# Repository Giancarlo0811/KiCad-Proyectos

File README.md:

# KiCad-Proyectos
Repositorio con diseños de PCB usando KiCad 8.0

## Diseños PCB

- ### [P1 Linterna LED](./P1_LED_torch)

- ### [P2 Fuente de Poder para Protoboard](./P2_Protoboard_Power_Supply/)

- ### [P3 Reloj Matriz LED 4x8x8 ](./P3_4x8x8_LED_Matrix_Clock/)

- ### [P4 Regulador de Voltaje Lineal de 5V](./P4_Regulador_Voltaje_5V/)

- ### [P5 Datalogger con Microcontrolador](./P5_MCU_Datalogger/)

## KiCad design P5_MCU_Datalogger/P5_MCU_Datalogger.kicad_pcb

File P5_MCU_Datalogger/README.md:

# P5 MCU Datalogger
Diseño de PCB para un datalogger con microcontrolador. El datalogger se basa en un microcontrolador Atmega 328P-AU y cuenta con dos EEPROMs y un reloj en tiempo real.
Componentes adicionales en la placa, como LEDs de estado con sus resistencias, dos osciladores de cristal, conectores y capacitores.

## Esquemático

## Layout

## PCB

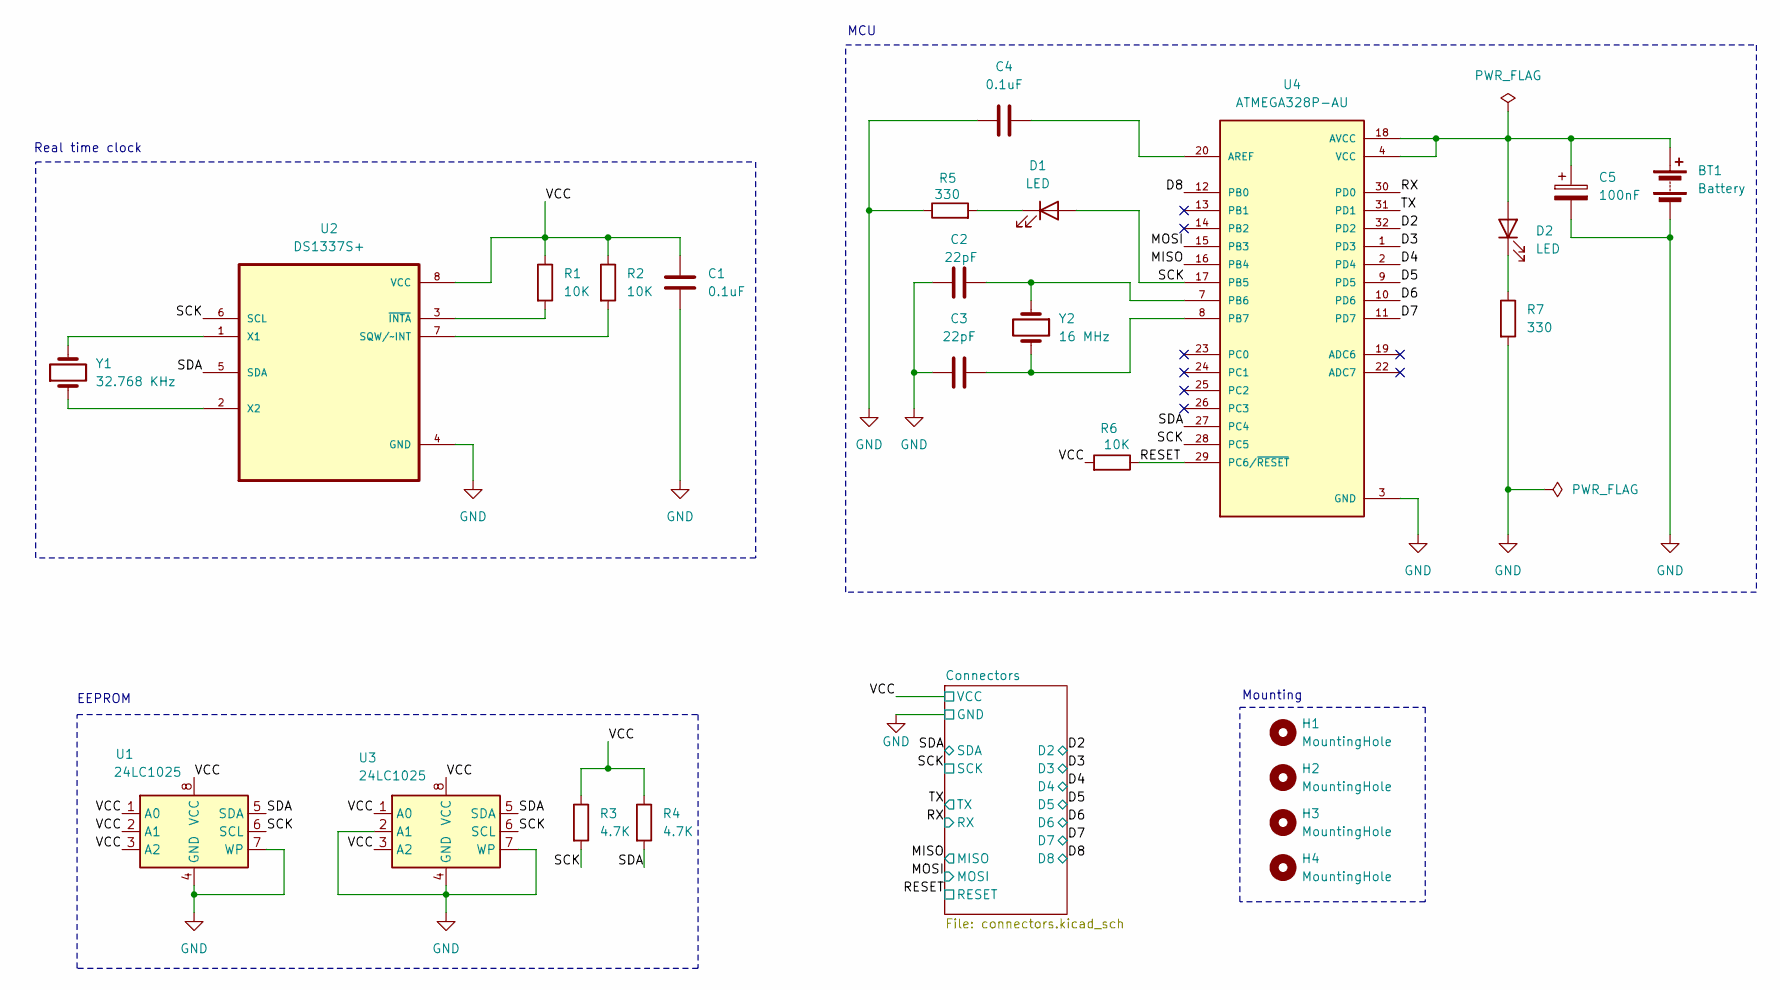
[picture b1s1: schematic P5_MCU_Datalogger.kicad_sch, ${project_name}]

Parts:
BT1: Battery; PinHeader_1x02_P2.54mm_Vertical
C1, C4: 0.1uF; C_0805_2012Metric
C2, C3: 22pF; C_0805_2012Metric
C5: 100nF; CP_Elec_3x5.3
D1, D2: LED; LED_0805_2012Metric
H1, H2, H3, H4: MountingHole; MountingHole_2.1mm
R1, R2, R6: 10K; R_0805_2012Metric
R3, R4: 4.7K; R_0805_2012Metric
R5, R7: 330; R_0805_2012Metric
U1, U3: 24LC1025; SOIC-8-1EP_3.9x4.9mm_P1.27mm_EP2.29x3mm
U2: DS1337S+; SOIC127P600X175-8N
U4: ATMEGA328P-AU; QFP80P900X900X120-32N; PARTREV 8271A
Y1: 32.768 KHz; Crystal_SMD_5032-2Pin_5.0x3.2mm_HandSoldering
Y2: 16 MHz; Crystal_SMD_5032-2Pin_5.0x3.2mm_HandSoldering

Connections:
/D2: U4.32 (PD2); also elsewhere on the board
/D3: U4.1 (PD3); also elsewhere on the board
/D4: U4.2 (PD4); also elsewhere on the board
/D5: U4.9 (PD5); also elsewhere on the board
/D6: U4.10 (PD6); also elsewhere on the board
/D7: U4.11 (PD7); also elsewhere on the board
/D8: U4.12 (PB0); also elsewhere on the board
/MISO: U4.16 (PB4); also elsewhere on the board
/MOSI: U4.15 (PB3); also elsewhere on the board
/RESET: R6.1, U4.29 (PC6/~RESET); also elsewhere on the board
/RX: U4.30 (PD0); also elsewhere on the board
/SCK: D1.2 (A), R3.2, U1.6 (SCL), U2.6 (SCL), U3.6 (SCL), U4.17 (PB5), U4.28 (PC5); also elsewhere on the board
/SDA: R4.2, U1.5 (SDA), U2.5 (SDA), U3.5 (SDA), U4.27 (PC4); also elsewhere on the board
/TX: U4.31 (PD1); also elsewhere on the board
GND: BT1.2 (-), C1.2, C2.1, C3.2, C4.2, C5.2, R5.1, R7.2, U1.4 (GND), U1.7 (WP), U2.4 (GND), U3.2 (A1), U3.4 (GND), U3.7 (WP), U4.3 (GND), U4.5 (GND), U4.21 (GND); also elsewhere on the board
unnamed: D1.1 (K), R5.2
unnamed: D2.1 (K), R7.1
unnamed: R2.2, U2.7 (SQW/~INT)
unnamed: U2.1 (X1), Y1.2
unnamed: U2.2 (X2), Y1.1
unnamed: R1.2, U2.3 (~INTA)
unnamed: C4.1, U4.20 (AREF)
unnamed: C2.2, U4.7 (PB6), Y2.1
unnamed: C3.1, U4.8 (PB7), Y2.2

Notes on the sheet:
Mounting
MCU
EEPROM
Real time clock

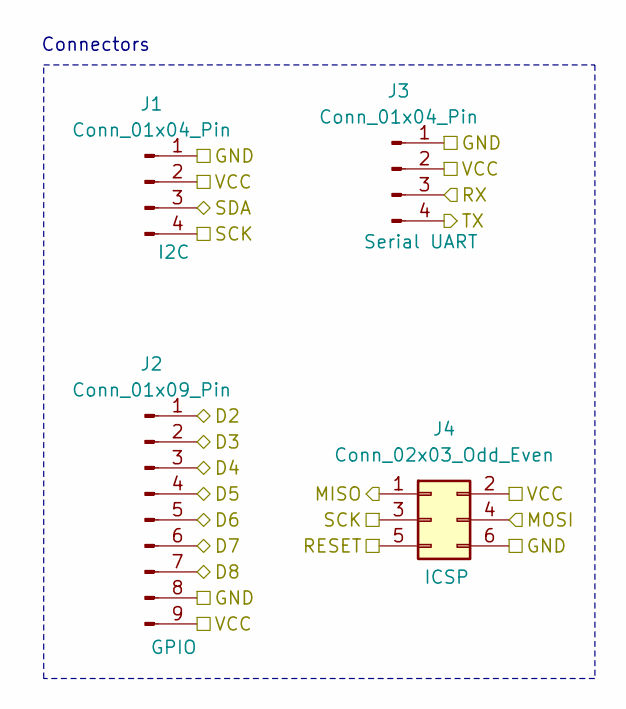
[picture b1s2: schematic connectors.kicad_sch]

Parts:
J1, J3: Conn_01x04_Pin; PinHeader_1x04_P2.54mm_Vertical
J2: Conn_01x09_Pin; PinHeader_1x09_P2.54mm_Vertical
J4: Conn_02x03_Odd_Even; PinHeader_2x03_P2.54mm_Vertical

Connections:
/D2: J2.1; also elsewhere on the board
/D3: J2.2; also elsewhere on the board
/D4: J2.3; also elsewhere on the board
/D5: J2.4; also elsewhere on the board
/D6: J2.5; also elsewhere on the board
/D7: J2.6; also elsewhere on the board
/D8: J2.7; also elsewhere on the board
/MISO: J4.1; also elsewhere on the board
/MOSI: J4.4; also elsewhere on the board
/RESET: J4.5; also elsewhere on the board
/RX: J3.3; also elsewhere on the board
/SCK: J1.4, J4.3; also elsewhere on the board
/SDA: J1.3; also elsewhere on the board
/TX: J3.4; also elsewhere on the board
GND: J1.1, J2.8, J3.1, J4.6; also elsewhere on the board

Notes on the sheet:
Connectors

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
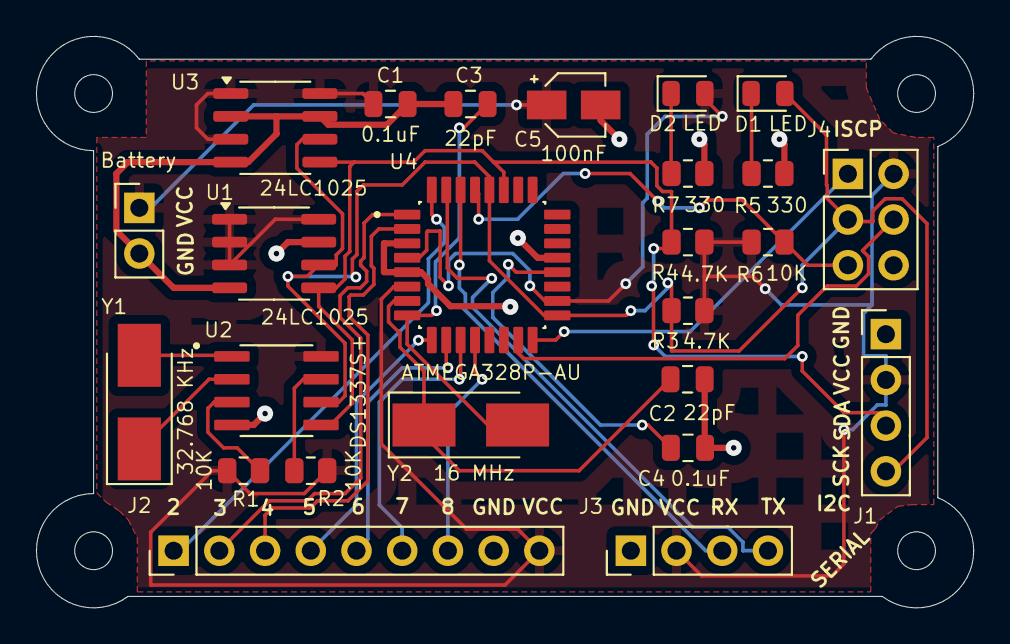
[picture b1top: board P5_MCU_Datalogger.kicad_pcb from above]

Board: 2 copper layers, 52.1 x 31.7 mm, 29 parts (0 on the bottom side), 25 nets.

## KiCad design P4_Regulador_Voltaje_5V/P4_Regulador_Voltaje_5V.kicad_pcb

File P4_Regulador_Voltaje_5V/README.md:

# P4 5V Voltage Regulator
Diseño de PCB para circuito regulador de 5V utilizando el regulador lineal LM2940.

- Voltaje de entrada: 7-35V DC

- Voltaje de salida regulado: 5V DC

## Esquemático

## Layout

## PCB

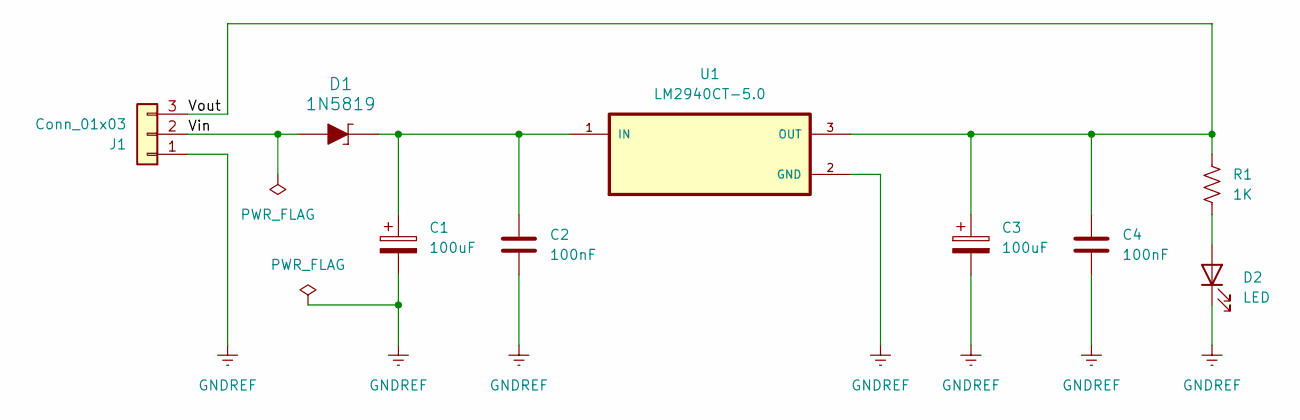
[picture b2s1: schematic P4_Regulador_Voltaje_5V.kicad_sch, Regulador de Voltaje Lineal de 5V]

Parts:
C1, C3: 100uF; CP_Radial_D10.0mm_P5.00mm
C2, C4: 100nF; C_Disc_D5.0mm_W2.5mm_P5.00mm
D1: 1N5819; D_DO-35_SOD27_P10.16mm_Horizontal; MPN 1N5819; Digi-Key_PN 1N5819FSCT-ND
D2: LED; LED_D5.0mm
J1: Conn_01x03; PinHeader_1x03_P2.54mm_Horizontal
R1: 1K; R_Axial_DIN0207_L6.3mm_D2.5mm_P7.62mm_Horizontal
U1: LM2940CT-5.0; TO254P1054X470X1955-3

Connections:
/Vin: D1.2, J1.2
/Vout: C3.1, C4.1, J1.3, R1.1, U1.3 (OUT)
GNDREF: C1.2, C2.2, C3.2, C4.2, D2.1 (K), J1.1, U1.2 (GND)
unnamed: D2.2 (A), R1.2
unnamed: C1.1, C2.1, D1.1, U1.1 (IN)

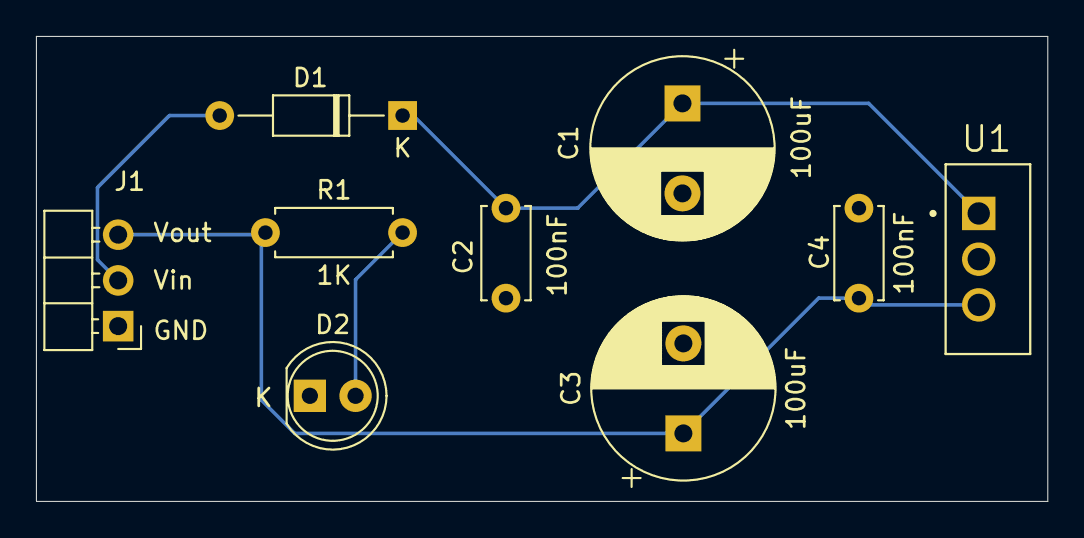
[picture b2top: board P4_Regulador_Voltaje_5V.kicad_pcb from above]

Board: 2 copper layers, 56.2 x 25.8 mm, 9 parts (0 on the bottom side), 5 nets.

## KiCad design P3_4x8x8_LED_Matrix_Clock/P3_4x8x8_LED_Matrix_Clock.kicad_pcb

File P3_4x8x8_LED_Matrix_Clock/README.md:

# P3 4x8x8 LED Matrix Clock
Diseño de PCB que puede tener cuatro pantallas de matriz LED de 8x8 controladas por un Arduino Pro
mini. 

La placa también incluye dos botones a los que se pueden asignar funciones arbitrarias.
Un posible uso puede ser un temporizador Pomodoro: Un botón para seleccionar la duración de la vuelta (por ejemplo, 15, 20 o 25 minutos) y el otro para reiniciar el temporizador. Cuando se acabe el tiempo establecido, la pantalla parpadeará para avisar.

## Esquemático

## Layout

## PCB

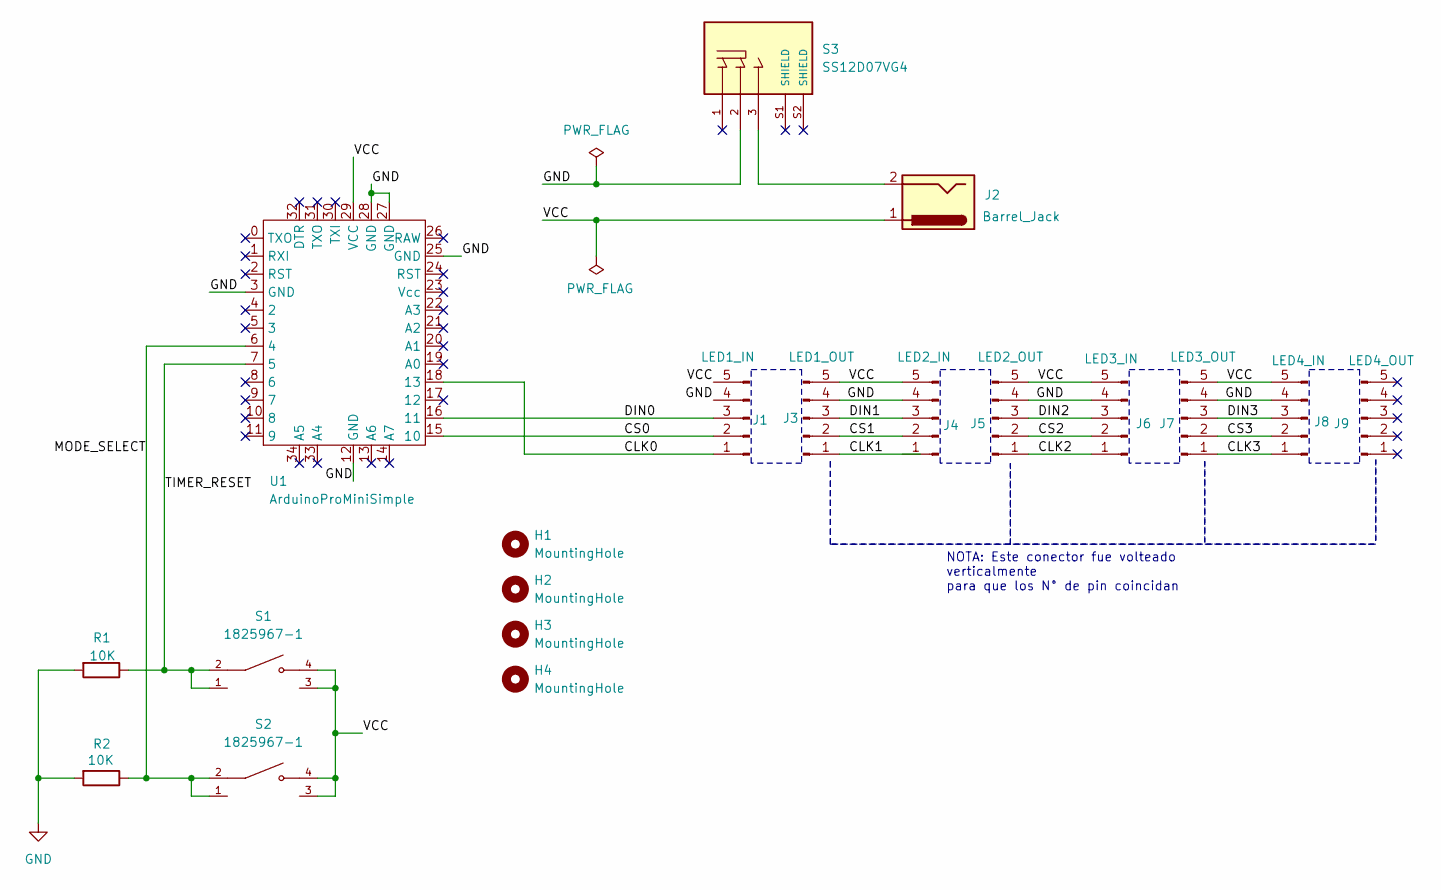
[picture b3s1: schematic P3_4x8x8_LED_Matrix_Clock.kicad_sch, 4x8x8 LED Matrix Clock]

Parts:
H1, H2, H3, H4: MountingHole; MountingHole_2.5mm
J1: LED1_IN; PinHeader_1x05_P2.54mm_Vertical
J2: Barrel_Jack; BarrelJack_Horizontal
J3: LED1_OUT; PinSocket_1x05_P2.54mm_Vertical
J4: LED2_IN; PinSocket_1x05_P2.54mm_Vertical
J5: LED2_OUT; PinSocket_1x05_P2.54mm_Vertical
J6: LED3_IN; PinSocket_1x05_P2.54mm_Vertical
J7: LED3_OUT; PinSocket_1x05_P2.54mm_Vertical
J8: LED4_IN; PinSocket_1x05_P2.54mm_Vertical
J9: LED4_OUT; PinSocket_1x05_P2.54mm_Vertical
R1, R2: 10K; R_Axial_DIN0204_L3.6mm_D1.6mm_P7.62mm_Horizontal
S1, S2: 1825967-1; SW_1825967-1
S3: SS12D07VG4; SW_SS12D07VG4; PARTREV 1
U1: ArduinoProMiniSimple; ArduinoProMiniCustom

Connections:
/CLK0: J1.1, U1.18 (13)
/CLK1: J3.1
/CLK2: J5.1, J6.1
/CLK3: J7.1, J8.1
/CS0: J1.2, U1.15 (10)
/CS1: J3.2, J4.2
/CS2: J5.2, J6.2
/CS3: J7.2, J8.2
/DIN0: J1.3, U1.16 (11)
/DIN1: J3.3, J4.3
/DIN2: J5.3, J6.3
/DIN3: J7.3, J8.3
/MODE_SELECT: R2.1, S2.1, S2.2, U1.6 (4)
/TIMER_RESET: R1.1, S1.1, S1.2, U1.7 (5)
/VCC: J1.5, J2.1, J3.5, J4.5, J5.5, J6.5, J7.5, J8.5, S1.3, S1.4, S2.3, S2.4, U1.29 (VCC)
GND: J1.4, J3.4, J4.4, J5.4, J6.4, J7.4, J8.4, R1.2, R2.2, S3.2, U1.3 (GND), U1.12 (GND), U1.25 (GND), U1.27 (GND), U1.28 (GND)
unnamed: J2.2, S3.3

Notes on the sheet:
NOTA: Este conector fue volteado verticalmente para que los N° de pin coincidan

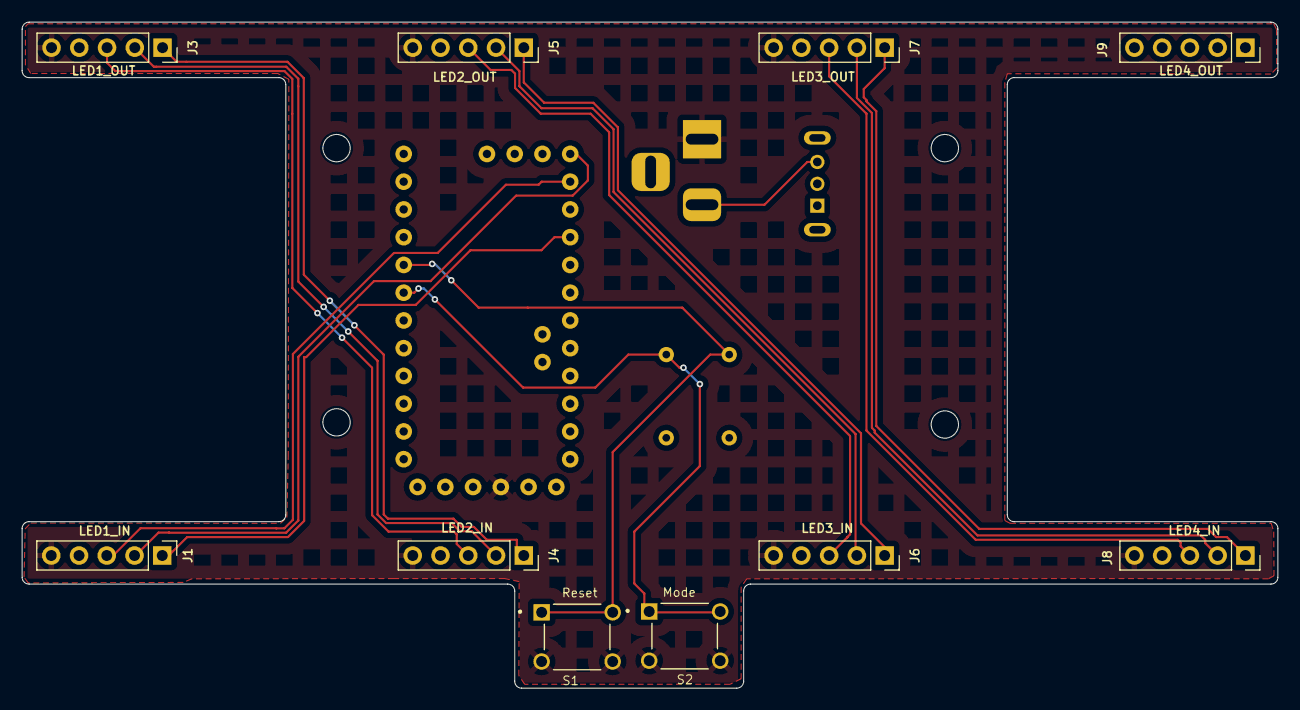
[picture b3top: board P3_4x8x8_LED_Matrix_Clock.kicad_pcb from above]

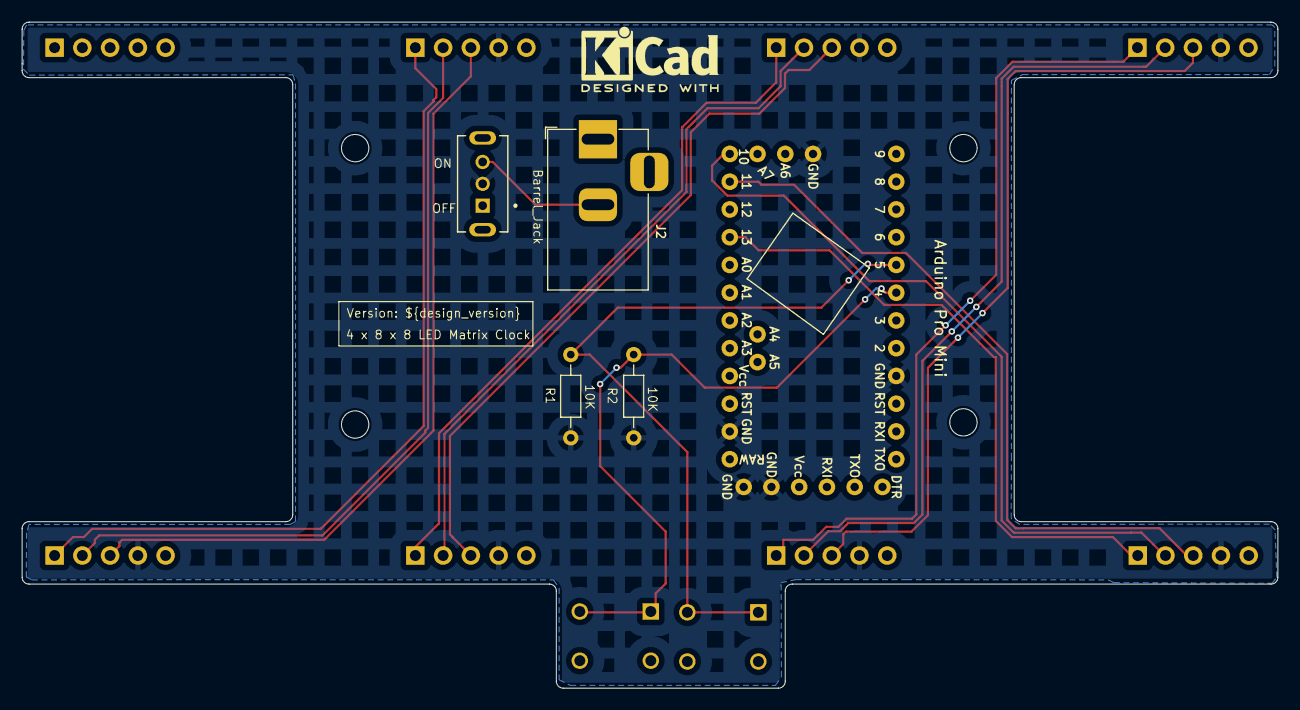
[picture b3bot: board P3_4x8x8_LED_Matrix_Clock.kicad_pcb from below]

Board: 2 copper layers, 114.9 x 61.0 mm, 20 parts (6 on the bottom side), 16 nets.

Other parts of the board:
Kicad_Logo: KiCad-Logo2_5mm_SilkScreen

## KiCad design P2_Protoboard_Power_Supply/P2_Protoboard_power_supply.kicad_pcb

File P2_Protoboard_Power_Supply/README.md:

# P1 Protoboard Power Supply
Diseño de una fuente de poder para protoboard.
- Puede conectarse directamente a la protoboard
- On/Off switch
- Puede proveer 5V y 3.3V
- Puede usar voltajes de una variedad de fuentes de alimentación, desde 6 V hasta 12 V.

## Esquemático

## Layout

## PCB

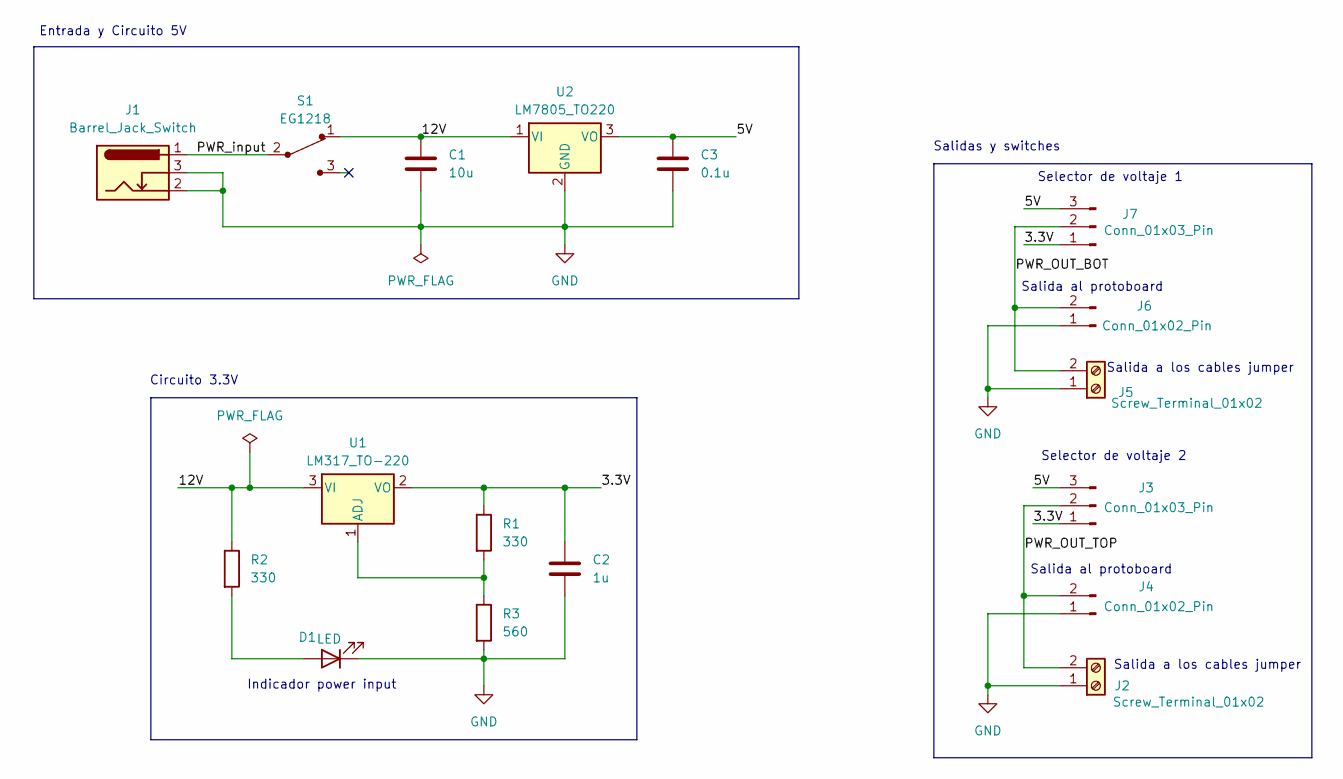
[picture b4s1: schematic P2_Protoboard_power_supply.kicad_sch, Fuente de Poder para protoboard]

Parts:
C1: 10u; C_Disc_D3.0mm_W1.6mm_P2.50mm
C2: 1u; C_Disc_D3.0mm_W1.6mm_P2.50mm
C3: 0.1u; C_Disc_D3.0mm_W1.6mm_P2.50mm
D1: LED; LED_D5.0mm
J1: Barrel_Jack_Switch; BarrelJack_Horizontal
J2, J5: Screw_Terminal_01x02; TerminalBlock_bornier-2_P5.08mm
J3, J7: Conn_01x03_Pin; PinHeader_1x03_P2.54mm_Vertical
J4, J6: Conn_01x02_Pin; PinHeader_1x02_P2.54mm_Vertical
R1, R2: 330; R_Axial_DIN0204_L3.6mm_D1.6mm_P7.62mm_Horizontal
R3: 560; R_Axial_DIN0204_L3.6mm_D1.6mm_P7.62mm_Horizontal
S1: EG1218; Switch_Slide_11.6x4mm_EG1218; MPN EG1218; Digi-Key_PN EG1903-ND
U1: LM317_TO-220; TO-220-3_Vertical
U2: LM7805_TO220; TO-220-3_Vertical

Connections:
/3.3V: C2.1, J3.1, J7.1, R1.1, U1.2 (VO)
/5V: C3.1, J3.3, J7.3, U2.3 (VO)
/12V: C1.1, R2.1, S1.1, U1.3 (VI), U2.1 (VI)
/PWR_OUT_BOT: J5.2, J6.2, J7.2
/PWR_OUT_TOP: J2.2, J3.2, J4.2
/PWR_input: J1.1, S1.2
GND: C1.2, C2.2, C3.2, D1.1 (K), J1.2, J1.3, J2.1, J4.1, J5.1, J6.1, R3.2, U2.2 (GND)
unnamed: D1.2 (A), R2.2
unnamed: R1.2, R3.1, U1.1 (ADJ)

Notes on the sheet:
Selector de voltaje 2
Salida a los cables jumper
Salidas y switches
Indicador power input
Selector de voltaje 1
Entrada y Circuito 5V
Circuito 3.3V
Salida al protoboard

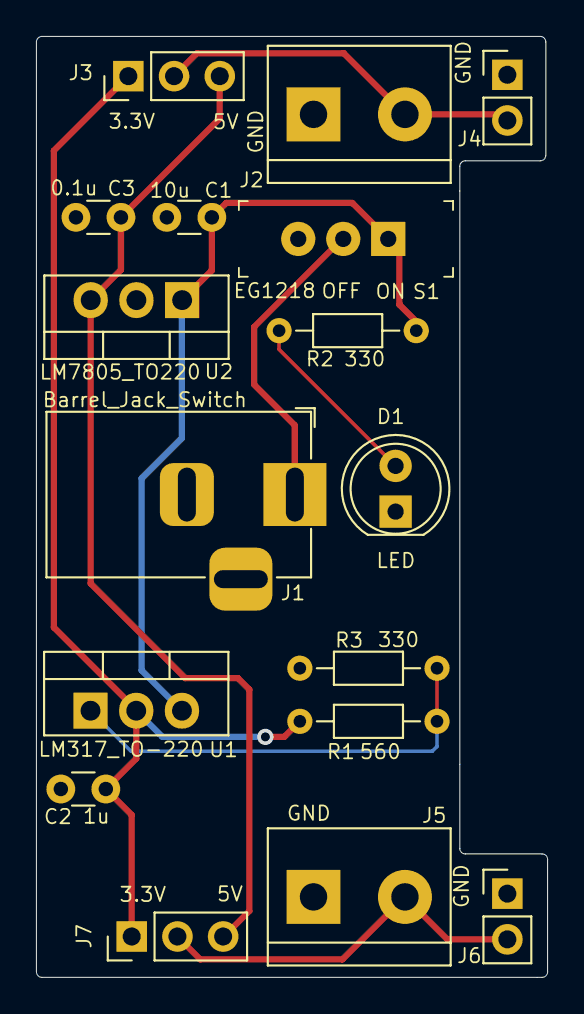
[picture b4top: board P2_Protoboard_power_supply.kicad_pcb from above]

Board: 2 copper layers, 28.4 x 52.3 mm, 17 parts (0 on the bottom side), 9 nets.

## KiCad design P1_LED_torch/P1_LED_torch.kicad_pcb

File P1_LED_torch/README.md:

# P1 LED Torch
Diseño simple de una Linterna LED para practicar con KiCad.

## Esquemático

## Layout

## PCB

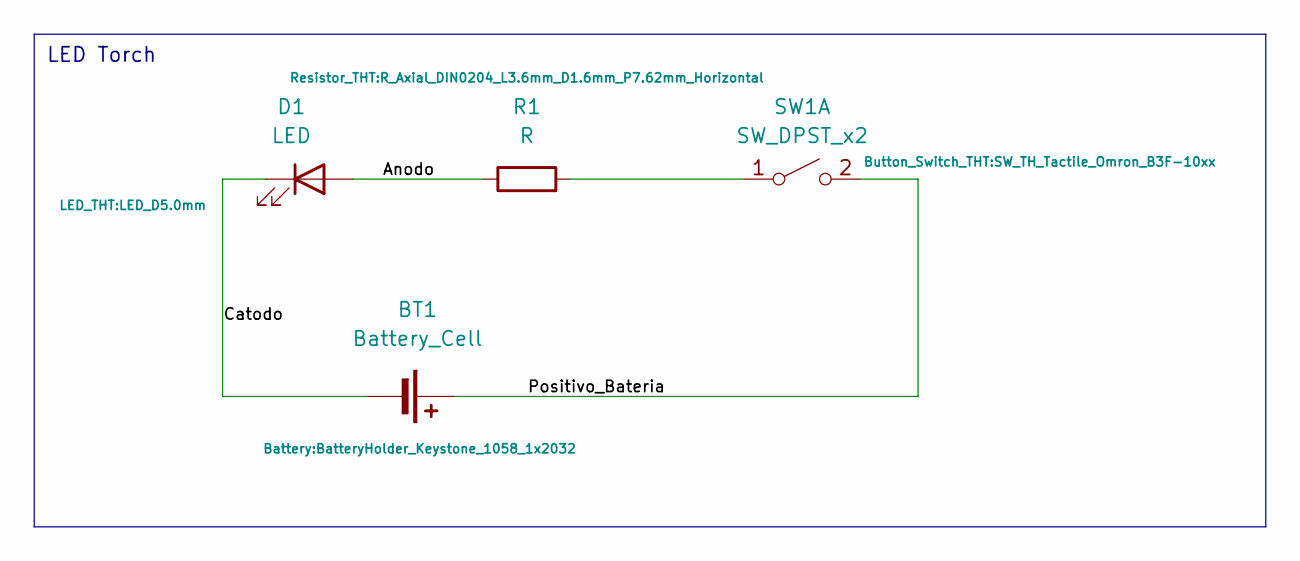
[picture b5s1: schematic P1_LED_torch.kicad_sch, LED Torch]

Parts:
BT1: Battery_Cell; BatteryHolder_Keystone_1058_1x2032
D1: LED; LED_D5.0mm
R1: R; R_Axial_DIN0204_L3.6mm_D1.6mm_P7.62mm_Horizontal
SW1: SW_DPST_x2; SW_TH_Tactile_Omron_B3F-10xx

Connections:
/Anodo: D1.2 (A), R1.1
/Catodo: BT1.2 (-), D1.1 (K)
/Positivo_Bateria: BT1.1 (+), SW1.2 (B)
unnamed: R1.2, SW1.1 (A)

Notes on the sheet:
LED Torch

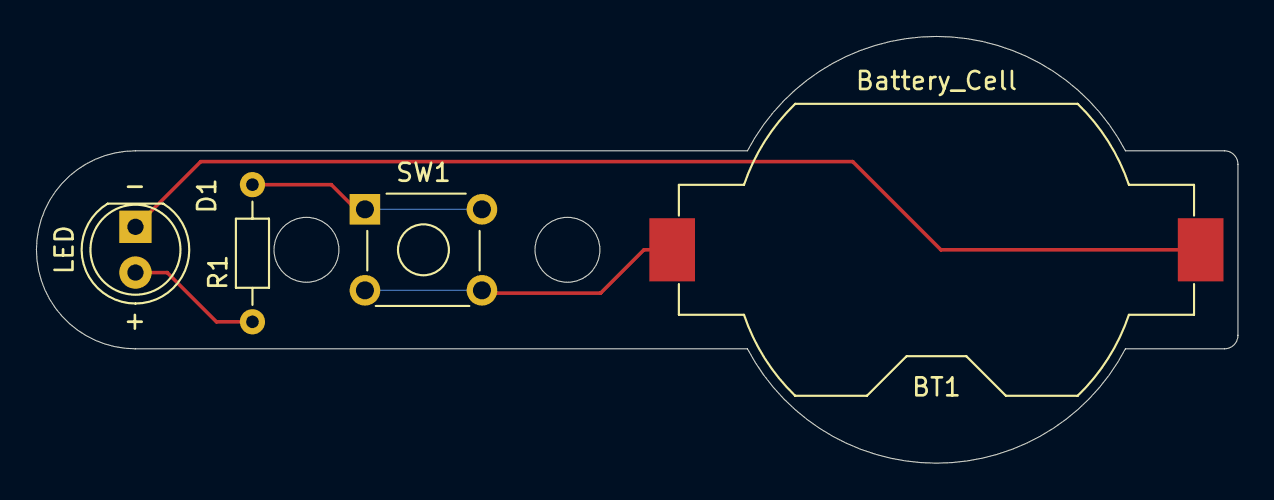
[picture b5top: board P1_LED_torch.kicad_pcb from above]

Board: 2 copper layers, 66.8 x 23.7 mm, 5 parts (1 on the bottom side), 4 nets.

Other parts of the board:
REF1: KiCad-Logo2_8mm_SilkScreen

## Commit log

2025-03-11 gitignore agregado
2025-05-24 readme actualizado
2026-02-02 first project commit
